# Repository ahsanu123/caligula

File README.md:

# 🥡 Introduction 

 <br/>
 
### 🎶 Useful Notes

```shell
To get started, you need to set up some environment variables by running: '. /home/ah/export-esp.sh'
This step must be done every time you open a new terminal.
See other methods for setting the environment in https://esp-rs.github.io/book/installation/riscv-and-xtensa.html#3-set-up-the-environment-variables
```

- to use usb from windows inside wsl you need bridge usb device from windows to wsl with `usbipd`

  ```shell
  C:\Windows\System32> usbipd list
  Connected:
  BUSID  VID:PID    DEVICE                                                        STATE
  1-1    feed:0ffa  USB Input Device                                              Not shared
  1-2    0000:3825  USB Input Device                                              Not shared
  1-4    0bda:0129  Realtek USB 2.0 Card Reader                                   Not shared
  1-5    13d3:56cb  USB2.0 HD IR UVC WebCam                                       Not shared
  1-6    1366:0101  J-Link driver                                                 Not shared
  1-10   8087:0026  Intel(R) Wireless Bluetooth(R)                                Not shared

  Persisted:
  GUID                                  DEVICE

  C:\Windows\System32> usbipd bind --busid 1-6

  C:\Windows\System32> usbipd attach --wsl --busid 1-6
  usbipd: info: Using WSL distribution 'Arch' to attach; the device will be available in all WSL 2 distributions.
  usbipd: info: Detected networking mode 'nat'.
  usbipd: info: Using IP address 172.27.144.1 to reach the host.

  C:\Windows\System32>
  ```

  then you can access the usb device as in linux

- run `get_esprs` to add needed compiler to system PATH (`alias get_esprs='export-esp.sh'`)
- to build release, flash, and monitor run `cargo run --release`, it will run runner `espflash  flash --monitor -L defmt` from Config.toml inside `.cargo` folder
- to run monitor only (no build) run `espflash monitor -L defmt --elf target/xtensa-esp32-none-elf/release/caligula`, you need add -L for logging format, and add --elf for defmt know about program.
- run `espflash board-info` to get connected board information
- to flash and run, `cargo run --release --bin rust_file_name.rs`
- embassy-sync blog -> https://blog.theembeddedrustacean.com/sharing-data-among-tasks-in-rust-embassy-synchronization-primitives

### 🧑‍🍳 Recipes

- esp-generate -> to scafold esp32 project [repo](https://github.com/esp-rs/esp-generate/)
- espup -> setup rust esp32 toolchain [repo](https://github.com/esp-rs/espup)
- defmt -> test like std rust in no_std [repo](https://github.com/knurling-rs/defmt)
- espflash -> to flashing firmware 
- probe-rs -> to debugging also able to flash

### 🪗 TODO Log

learn rust embassy ecosistem with esp-rs 

- ~~map all predefined SORE button and led~~
- ~~read multithread chapter in rust book~~
- ~~learn to make peripheral with hal~~
- learn about interupt and ~~dma~~
- ~~learn how embassy and esp-hal is connected~~
- ~~learn and explore embassy docs for esp32~~
- ~~read embassy_sync for multithread in embassy~~
- ~~learn embassy feature and learn embassy async~~
- search for match sensor and actuator
- make TMC2209 Stepper motor driver for actuator

### 🌴 Project Log

- 23 march 2025 20:02, basic esp rust setup with embassy, esp-println and defmt for logging is work
- ⛑️ TOOD: make project to have test like std rust with defmt, so its easier to create and unit testing in no_std
- 10 Mei 2025 13:06, done skiming https://docs.esp-rs.org/book
- 1 Mei 2026 18:10, finish routing phase one 

### 🌼 Reference 

- [esp no_std training](https://github.com/esp-rs/no_std-training)
- [official esp32 rust docs](https://docs.espressif.com/projects/rust/)
- [probe-rs](https://github.com/probe-rs/rusty-probe?tab=readme-ov-file)
- [rust-embedded](https://docs.rust-embedded.org/book/intro/tooling.html)
- [embassy-setup-on-esp32](https://pg3.dev/post/13)
- [plotter rs, console backend sample](https://github.com/plotters-rs/plotters/blob/master/plotters/examples/console.rs)
- [embassy-book](https://embassy.dev/book/)
- [esp-build](https://github.com/esp-rs/rust-build)
- https://github.com/zpg6/esp32-sdcard
- https://github.com/rust-embedded-community/embedded-sdmmc-rs
- [designing with ph electrodes](https://www.ti.com/lit/an/snoa529a/snoa529a.pdf)
- [tauri sidecar](https://tauri.app/develop/sidecar/)

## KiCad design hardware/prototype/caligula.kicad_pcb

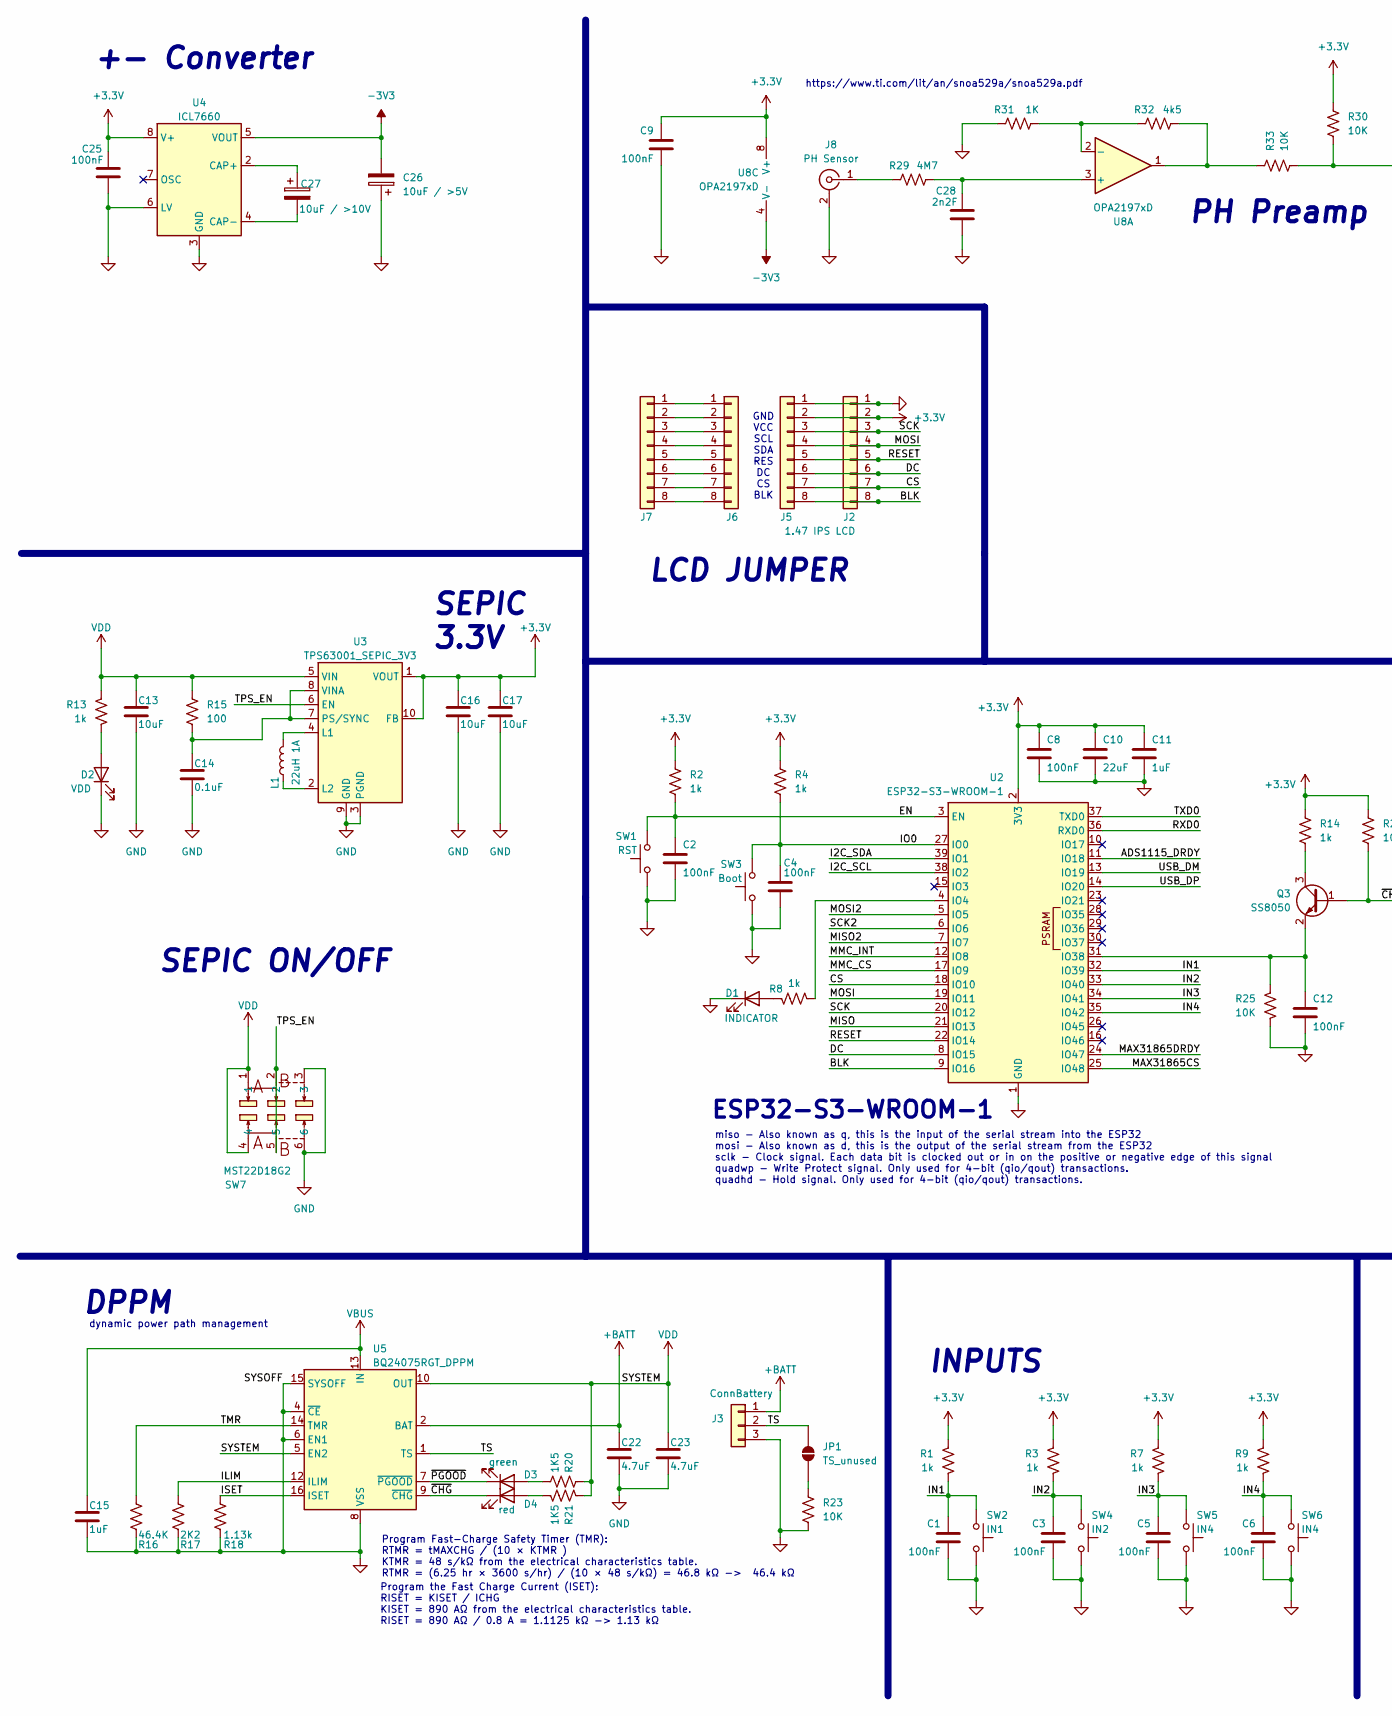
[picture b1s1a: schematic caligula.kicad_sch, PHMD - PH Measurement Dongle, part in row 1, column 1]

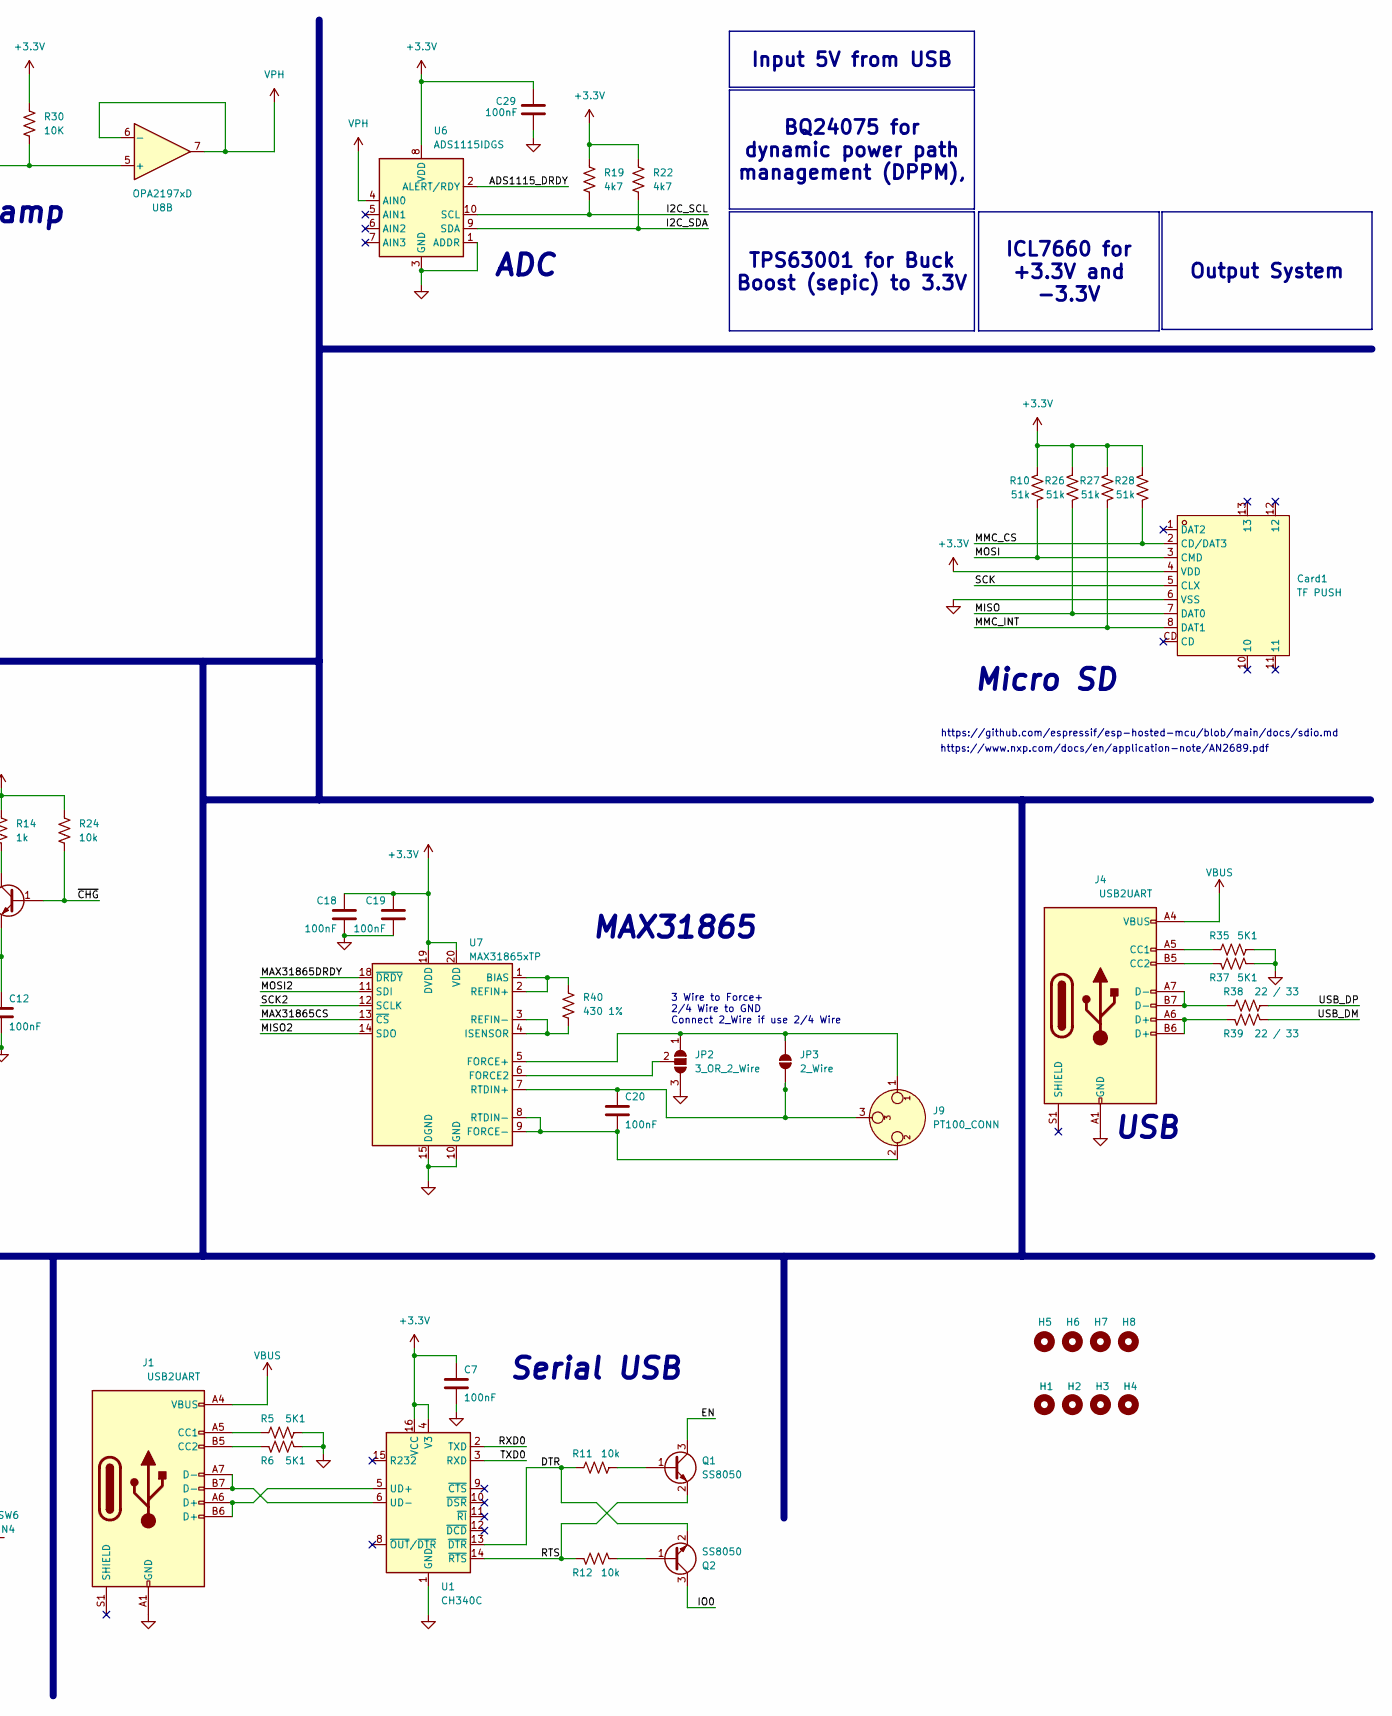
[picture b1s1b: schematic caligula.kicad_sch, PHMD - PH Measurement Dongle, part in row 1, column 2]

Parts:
C1, C2, C3, C4, C5, C6, C7, C8, C9, C12, C18, C19, C20, C25, C29: 100nF; C_0805_2012Metric_Pad1.18x1.45mm_HandSolder
C10: 22uF; C_0805_2012Metric_Pad1.18x1.45mm_HandSolder
C11, C15: 1uF; C_0805_2012Metric_Pad1.18x1.45mm_HandSolder
C13, C16, C17: 10uF; C_0805_2012Metric_Pad1.18x1.45mm_HandSolder
C14: 0.1uF; C_0805_2012Metric_Pad1.18x1.45mm_HandSolder
C22, C23: 4.7uF; C_0805_2012Metric_Pad1.18x1.45mm_HandSolder
C26: 10uF / >5V; C_0805_2012Metric_Pad1.18x1.45mm_HandSolder
C27: 10uF / >10V; C_0805_2012Metric_Pad1.18x1.45mm_HandSolder
C28: 2n2F; C_0805_2012Metric_Pad1.18x1.45mm_HandSolder
Card1: TF PUSH; TF-SMD_TF-PUSH; MPN TF PUSH; LCSC Part C393941
D1: INDICATOR; LED_1206_3216Metric_Pad1.42x1.75mm_HandSolder
D2: VDD; LED_1206_3216Metric_Pad1.42x1.75mm_HandSolder
D3: green; LED_0805_2012Metric_Pad1.15x1.40mm_HandSolder
D4: red; LED_0805_2012Metric_Pad1.15x1.40mm_HandSolder
H1, H2, H3, H4: MountingHole; MountingHole_2mm
H5, H6, H7, H8: MountingHole; MountingHole_3.2mm_M3
J1, J4: USB2UART; USB_C_Receptacle_GCT_USB4110
J2: 1.47 IPS LCD; PinHeader_1x08_P2.54mm_Vertical
J3: ConnBattery; JST_XH_S3B-XH-A_1x03_P2.50mm_Horizontal
J5, J6, J7: lcd jumper; PinHeader_1x08_P2.54mm_Vertical
J8: PH Sensor; BNC_Amphenol_B6252HB-NPP3G-50_Horizontal
J9: PT100_CONN; Jack_XLR_Neutrik_NC3FAH-0_Horizontal
JP1: TS_unused; SolderJumper-2_P1.3mm_Open_RoundedPad1.0x1.5mm
JP2: 3_OR_2_Wire; SolderJumper-3_P1.3mm_Open_RoundedPad1.0x1.5mm
JP3: 2_Wire; SolderJumper-2_P1.3mm_Open_TrianglePad1.0x1.5mm
L1: 22uH 1A; L_Bourns_SRP7028A_7.3x6.6mm
Q1, Q2, Q3: SS8050; SOT-23_Handsoldering
R1, R2, R3, R4, R7, R8, R9, R13, R14: 1k; R_0805_2012Metric_Pad1.20x1.40mm_HandSolder
R5, R6, R35, R37: 5K1; R_0805_2012Metric_Pad1.20x1.40mm_HandSolder
R10, R26, R27, R28: 51k; R_0805_2012Metric_Pad1.20x1.40mm_HandSolder
R11, R12, R24: 10k; R_0805_2012Metric_Pad1.20x1.40mm_HandSolder
R15: 100; R_0805_2012Metric_Pad1.20x1.40mm_HandSolder
R16: 46.4K; R_0805_2012Metric_Pad1.20x1.40mm_HandSolder
R17: 2K2; R_0805_2012Metric_Pad1.20x1.40mm_HandSolder
R18: 1.13k; R_0805_2012Metric_Pad1.20x1.40mm_HandSolder
R19, R22: 4k7; R_0805_2012Metric_Pad1.20x1.40mm_HandSolder
R20, R21: 1K5; R_0805_2012Metric_Pad1.20x1.40mm_HandSolder
R23, R25, R30, R33: 10K; R_0805_2012Metric_Pad1.20x1.40mm_HandSolder
R29: 4M7; R_0805_2012Metric_Pad1.20x1.40mm_HandSolder
R31: 1K; R_0805_2012Metric_Pad1.20x1.40mm_HandSolder
R32: 4k5; R_0805_2012Metric_Pad1.20x1.40mm_HandSolder
R38, R39: 22 / 33; R_0805_2012Metric_Pad1.20x1.40mm_HandSolder
R40: 430 1%; R_0805_2012Metric_Pad1.20x1.40mm_HandSolder
SW1: RST; SW_SPST_EVQP7A
SW2: IN1; Kailh_socket_MX_reversible_platemount
SW3: Boot; SW_SPST_EVQP7A
SW4: IN2; Kailh_socket_MX_reversible_platemount
SW5, SW6: IN4; Kailh_socket_MX_reversible_platemount
SW7: MST22D18G2; SW-SMD_MST22D18G2; MPN MST22D18G2; LCSC Part C431544
U1: CH340C; SOIC-16_3.9x9.9mm_P1.27mm
U2: ESP32-S3-WROOM-1
U3: TPS63001_SEPIC_3V3; Texas_DRC0010J_ThermalVias
U4: ICL7660; SOIC-8_3.9x4.9mm_P1.27mm
U5: BQ24075RGT_DPPM; VQFN-16-1EP_3x3mm_P0.5mm_EP1.6x1.6mm
U6: ADS1115IDGS; TSSOP-10_3x3mm_P0.5mm
U7: MAX31865xTP; TQFN-20-1EP_5x5mm_P0.65mm_EP3.25x3.25mm
U8: OPA2197xD; SOIC-8_3.9x4.9mm_P1.27mm

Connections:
+3.3V: C7.1, C8.1, C9.1, C10.1, C11.1, C16.1, C17.1, C18.1, C19.1, C25.1, C29.1, Card1.4 (VDD), J2.2, J5.2, R1.1, R2.1, R3.1, R4.1, R7.1, R9.1, R10.1, R14.1, R19.1, R22.1, R24.1, R26.1, R27.1, R28.1, R30.1, U1.4 (V3), U1.16 (VCC), U2.2 (3V3), U3.1 (VOUT), U3.10 (FB), U4.8 (V+), U6.8 (VDD), U7.19 (DVDD), U7.20 (VDD), U8.8 (V+)
+BATT: C22.1, J3.1, U5.2 (BAT), U5.3 (BAT)
-3V3: C26.2, U4.5 (VOUT), U8.4 (V-)
/ADS1115_DRDY: U2.11 (IO18), U6.2 (ALERT/RDY)
/BLK: J2.8, J5.8, U2.9 (IO16)
/CS: J2.7, J5.7, U2.18 (IO10)
/DC: J2.6, J5.6, U2.8 (IO15)
/DTR: Q2.2 (E), R11.2, U1.13 (~DTR)
/EN: C2.1, Q1.3 (C), R2.2, SW1.2, U2.3 (EN)
/I2C_SCL: R19.2, U2.38 (IO2), U6.10 (SCL)
/I2C_SDA: R22.2, U2.39 (IO1), U6.9 (SDA)
/ILIM: R17.1, U5.12 (ILIM)
/IN1: C1.1, R1.2, SW2.2, U2.32 (IO39)
/IN2: C3.1, R3.2, SW4.2, U2.33 (IO40)
/IN3: C5.1, R7.2, SW5.2, U2.34 (IO41)
/IN4: C6.1, R9.2, SW6.2, U2.35 (IO42)
/IO0: C4.1, Q2.3 (C), R4.2, SW3.2, U2.27 (IO0)
/ISET: R18.1, U5.16 (ISET)
/MAX31865CS: U2.25 (IO48), U7.13 (~CS)
/MAX31865DRDY: U2.24 (IO47), U7.18 (~DRDY)
/MISO: Card1.7 (DAT0), R26.2, U2.21 (IO13)
/MISO2: U2.7 (IO7), U7.14 (SDO)
/MMC_CS: Card1.2 (CD/DAT3), R28.2, U2.17 (IO9)
/MMC_INT: Card1.8 (DAT1), R27.2, U2.12 (IO8)
/MOSI: Card1.3 (CMD), J2.4, J5.4, R10.2, U2.19 (IO11)
/MOSI2: U2.5 (IO5), U7.11 (SDI)
/RESET: J2.5, J5.5, U2.22 (IO14)
/RTS: Q1.2 (E), R12.2, U1.14 (~RTS)
/RXD0: U1.2 (TXD), U2.36 (RXD0)
/SCK: Card1.5 (CLX), J2.3, J5.3, U2.20 (IO12)
/SCK2: U2.6 (IO6), U7.12 (SCLK)
/TMR: R16.1, U5.14 (TMR)
/TPS_EN: SW7.2, SW7.5, U3.6 (EN)
/TS: J3.2, JP1.2 (B), U5.1 (TS)
/TXD0: U1.3 (RXD), U2.37 (TXD0)
/USB_DM: R39.1, U2.13 (IO19)
/USB_DP: R38.1, U2.14 (IO20)
/~CHG: D4.1 (K), Q3.1 (B), R24.2, U5.9 (~CHG)
/~PGOOD: D3.1 (K), U5.7 (~PGOOD)
GND: C1.2, C2.2, C3.2, C4.2, C5.2, C6.2, C7.2, C8.2, C9.2, C10.2, C11.2, C12.2, C13.2, C14.2, C15.2, C16.2, C17.2, C18.2, C19.2, C22.2, C23.2, C25.2, C26.1, C28.2, C29.2, Card1.6 (VSS), D1.1 (K), D2.1 (K), J1.A1 (GND), J1.A12 (GND), J1.B1 (GND), J1.B12 (GND), J2.1, J3.3, J4.A1 (GND), J4.A12 (GND), J4.B1 (GND), J4.B12 (GND), J5.1, J8.2 (Ext), JP2.3 (B), R5.1, R6.1, R16.2, R17.2, R18.2, R23.2, R25.2, R31.2, R35.1, R37.1, SW1.1, SW2.1, SW3.1, SW4.1, SW5.1, SW6.1, SW7.3, SW7.6, U1.1 (GND), U2.1 (GND), U2.40 (GND), U2.41 (GND), U3.3 (PGND), U3.9 (GND), U3.11 (PGND), U4.3 (GND), U4.6 (LV), U5.4 (~CE), U5.6 (EN1), U5.8 (VSS), U5.15 (SYSOFF), U5.17 (VSS), U6.1 (ADDR), U6.3 (GND), U7.10 (GND), U7.15 (DGND), U7.16 (GND), U7.21 (GND)
unnamed: D1.2 (A), R8.1
unnamed: D2.2 (A), R13.2
unnamed: D3.2 (A), R20.1
unnamed: D4.2 (A), R21.1
unnamed: J1.A5 (CC1), R5.2
unnamed: J1.B5 (CC2), R6.2
unnamed: J4.A5 (CC1), R35.2
unnamed: J4.B5 (CC2), R37.2
unnamed: J4.A6 (D+), J4.B6 (D+), R39.2
unnamed: J4.A7 (D-), J4.B7 (D-), R38.2
unnamed: J6.1, J7.1
unnamed: J6.2, J7.2
unnamed: J6.3, J7.3
unnamed: J6.4, J7.4
unnamed: J6.5, J7.5
unnamed: J6.6, J7.6
unnamed: J6.7, J7.7
unnamed: J6.8, J7.8
unnamed: J8.1 (In), R29.2
unnamed: JP1.1 (A), R23.1
unnamed: J9.1, JP2.1 (A), JP3.2 (B), U7.5 (FORCE+)
unnamed: JP2.2 (C), U7.6 (FORCE2)
unnamed: C20.1, J9.3, JP3.1 (A), U7.7 (RTDIN+)
unnamed: Q1.1 (B), R11.1
unnamed: Q2.1 (B), R12.1
unnamed: Q3.3 (C), R14.2
unnamed: C12.1, Q3.2 (E), R25.1, U2.31 (IO38)
unnamed: R32.1, R33.1, U8.1
unnamed: J1.A6 (D+), J1.B6 (D+), U1.5 (UD+)
unnamed: J1.A7 (D-), J1.B7 (D-), U1.6 (UD-)
unnamed: R8.2, U2.4 (IO4)
unnamed: L1.2, U3.4 (L1)
unnamed: L1.1, U3.2 (L2)
unnamed: C14.1, R15.2, U3.7 (PS/SYNC), U3.8 (VINA)
unnamed: C27.1, U4.2 (CAP+)
unnamed: C27.2, U4.4 (CAP-)
unnamed: R40.1, U7.1 (BIAS), U7.2 (REFIN+)
unnamed: C20.2, J9.2, U7.8 (RTDIN-), U7.9 (FORCE-)
unnamed: R40.2, U7.3 (REFIN-), U7.4 (ISENSOR)
unnamed: C28.1, R29.1, U8.3 (+)
unnamed: R31.1, R32.2, U8.2 (-)
unnamed: R30.2, R33.2, U8.5 (+)
VBUS: C15.1, J1.A4 (VBUS), J1.A9 (VBUS), J1.B4 (VBUS), J1.B9 (VBUS), J4.A4 (VBUS), J4.A9 (VBUS), J4.B4 (VBUS), J4.B9 (VBUS), U5.13 (IN)
VDD: C13.1, C23.1, R13.1, R15.1, R20.2, R21.2, SW7.1, SW7.4, U3.5 (VIN), U5.5 (EN2), U5.10 (OUT), U5.11 (OUT)
VPH: U6.4 (AIN0), U8.6 (-), U8.7

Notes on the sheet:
ADC
dynamic power path management
SEPIC ON/OFF
https://www.nxp.com/docs/en/application-note/AN2689.pdf
PH Preamp
miso - Also known as q, this is the input of the serial stream into the ESP32 mosi - Also known as d, this is the output of the serial stream from the ESP32 sclk - Clock signal. Each data bit is clocked out or in on the positive or negative edge of this signal quadwp - Write Protect signal. Only us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
ESP32-S3-WROOM-1
Serial USB
Program the Fast Charge Current (ISET): RISET = KISET / ICHG KISET = 890 AΩ from the electrical characteristics table. RISET = 890 AΩ / 0.8 A = 1.1125 kΩ -> 1.13 kΩ
3 Wire to Force+ 2/4 Wire to GND Connect 2_Wire if use 2/4 Wire
USB
+- Converter
https://www.ti.com/lit/an/snoa529a/snoa529a.pdf
DPPM
GND VCC SCL SDA RES DC CS BLK
https://github.com/espressif/esp-hosted-mcu/blob/main/docs/sdio.md
MAX31865
INPUTS
LCD JUMPER
SEPIC 3.3V
Micro SD
Program Fast-Charge Safety Timer (TMR): RTMR = tMAXCHG / (10 × KTMR ) KTMR = 48 s/kΩ from the electrical characteristics table. RTMR = (6.25 hr × 3600 s/hr) / (10 × 48 s/kΩ) = 46.8 kΩ -> 46.4 kΩ
Output System
TPS63001 for Buck Boost (sepic) to 3.3V
ICL7660 for +3.3V and -3.3V
Input 5V from USB
BQ24075 for dynamic power path management (DPPM),

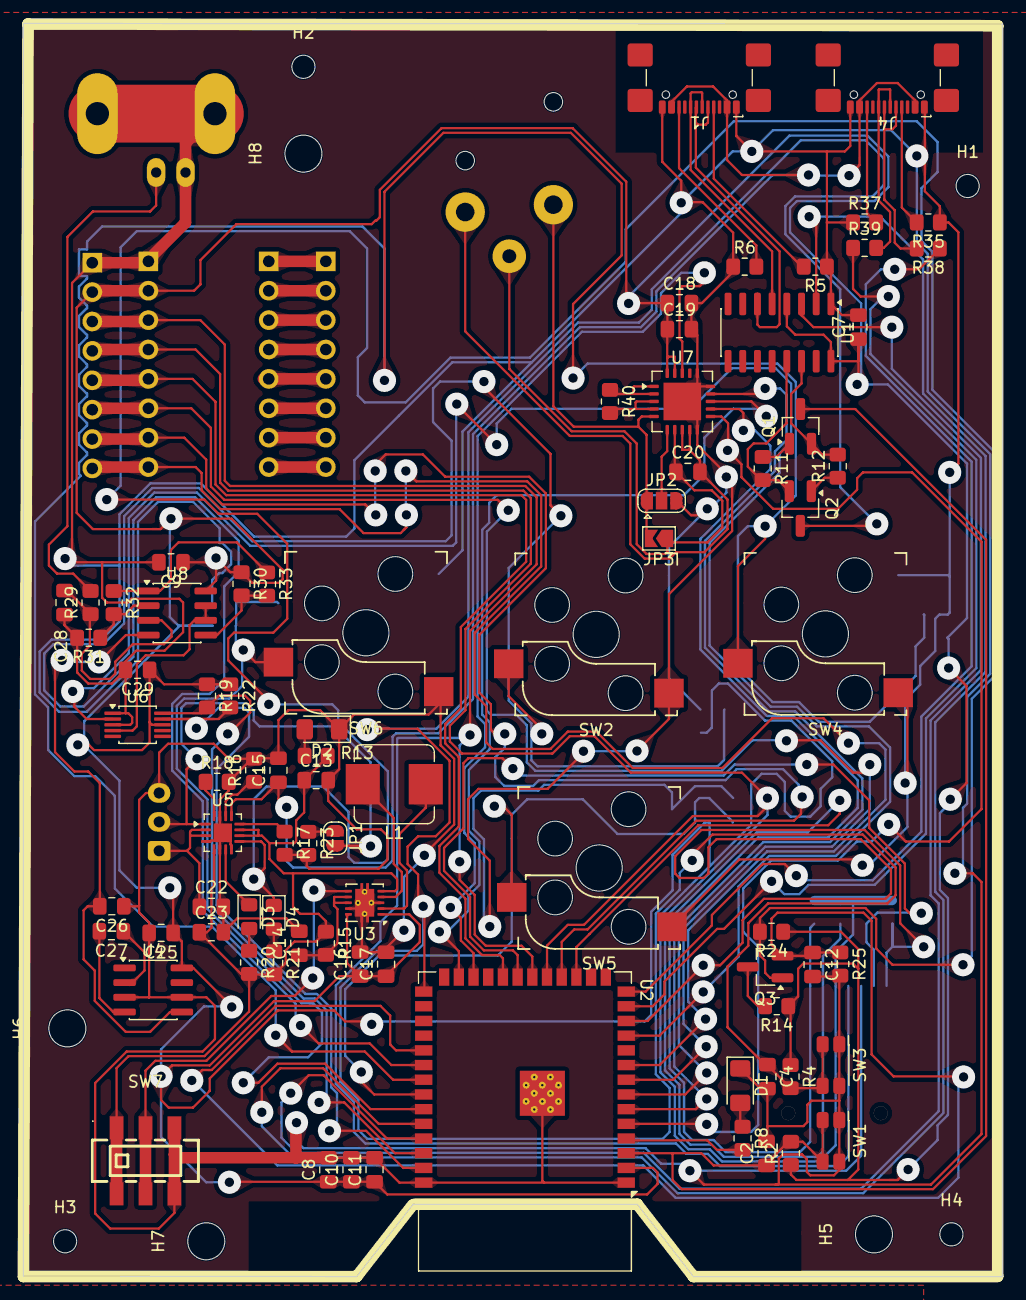
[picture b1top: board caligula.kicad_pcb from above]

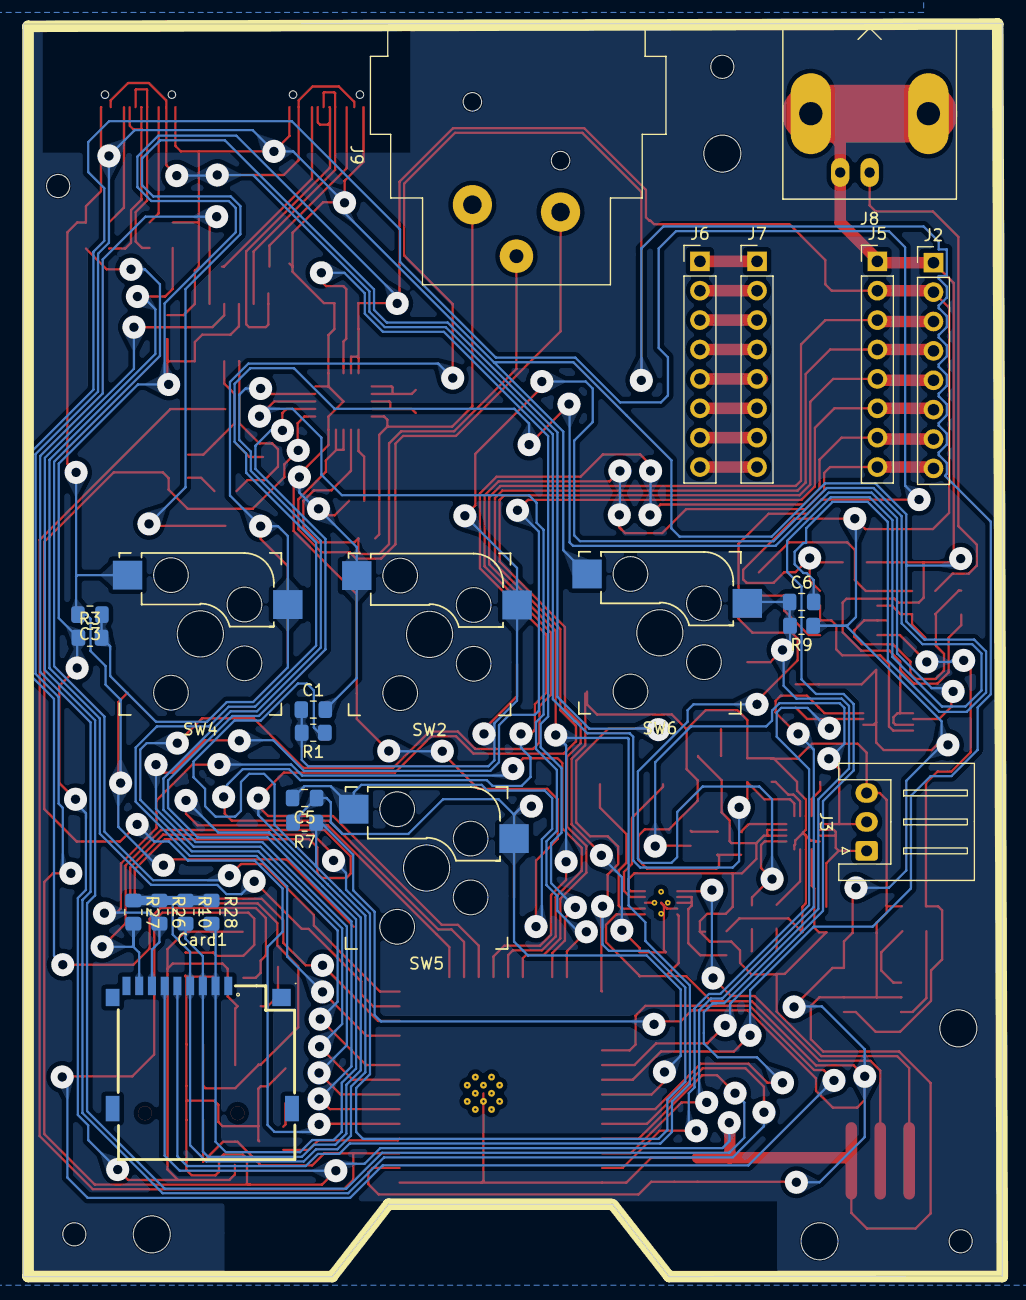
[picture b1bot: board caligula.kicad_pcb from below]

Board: 2 copper layers, 84.6 x 108.3 mm, 109 parts (24 on the bottom side), 85 nets.

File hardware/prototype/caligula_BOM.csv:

"Reference","Qty","Value","DNP","Exclude from BOM","Exclude from Board","Footprint","Datasheet"
"C1,C2,C3,C4,C5,C6,C7,C8,C9,C12,C18,C19,C20,C25,C29","15","100nF","","","","Capacitor_SMD:C_0805_2012Metric_Pad1.18x1.45mm_HandSolder",""
"C10","1","22uF","","","","Capacitor_SMD:C_0805_2012Metric_Pad1.18x1.45mm_HandSolder",""
"C11,C15","2","1uF","","","","Capacitor_SMD:C_0805_2012Metric_Pad1.18x1.45mm_HandSolder",""
"C13,C16,C17","3","10uF","","","","Capacitor_SMD:C_0805_2012Metric_Pad1.18x1.45mm_HandSolder",""
"C14","1","0.1uF","","","","Capacitor_SMD:C_0805_2012Metric_Pad1.18x1.45mm_HandSolder",""
"C22,C23","2","4.7uF","","","","Capacitor_SMD:C_0805_2012Metric_Pad1.18x1.45mm_HandSolder",""
"C26","1","10uF / >5V","","","","Capacitor_SMD:C_0805_2012Metric_Pad1.18x1.45mm_HandSolder",""
"C27","1","10uF / >10V","","","","Capacitor_SMD:C_0805_2012Metric_Pad1.18x1.45mm_HandSolder",""
"C28","1","2n2F","","","","Capacitor_SMD:C_0805_2012Metric_Pad1.18x1.45mm_HandSolder",""
"Card1","1","TF PUSH","","","","easyeda2kicad:TF-SMD_TF-PUSH","https://lcsc.com/product-detail/Connector-Card-Sockets_SHOU-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"
"D1","1","INDICATOR","","","","LED_SMD:LED_1206_3216Metric_Pad1.42x1.75mm_HandSolder",""
"D2","1","VDD","","","","LED_SMD:LED_1206_3216Metric_Pad1.42x1.75mm_HandSolder",""
"D3","1","green","","","","LED_SMD:LED_0805_2012Metric_Pad1.15x1.40mm_HandSolder",""
"D4","1","red","","","","LED_SMD:LED_0805_2012Metric_Pad1.15x1.40mm_HandSolder",""
"J1,J4","2","USB2UART","","","","Connector_USB:USB_C_Receptacle_GCT_USB4110","https://www.usb.org/sites/default/files/documents/usb_type-c.zip"
"J2","1","1.47 IPS LCD","","","","Connector_PinHeader_2.54mm:PinHeader_1x08_P2.54mm_Vertical",""
"J3","1","ConnBattery","","","","Connector_JST:JST_XH_S3B-XH-A_1x03_P2.50mm_Horizontal",""
"J5,J6,J7","3","lcd jumper","","","","Connector_PinHeader_2.54mm:PinHeader_1x08_P2.54mm_Vertical",""
"J8","1","PH Sensor","","","","Connector_Coaxial:BNC_Amphenol_B6252HB-NPP3G-50_Horizontal",""
"J9","1","PT100_CONN","","","","Connector_Audio:Jack_XLR_Neutrik_NC3FAH-0_Horizontal",""
"L1","1","22uH 1A","","","","Inductor_SMD:L_Bourns_SRP7028A_7.3x6.6mm",""
"Q1,Q2,Q3","3","SS8050","","","","Package_TO_SOT_SMD:SOT-23_Handsoldering","https://www.onsemi.com/pub/Collateral/BC818-D.pdf"
"R1,R2,R3,R4,R7,R8,R9,R13,R14","9","1k","","","","Resistor_SMD:R_0805_2012Metric_Pad1.20x1.40mm_HandSolder",""
"R5,R6,R35,R37","4","5K1","","","","Resistor_SMD:R_0805_2012Metric_Pad1.20x1.40mm_HandSolder",""
"R10,R26,R27,R28","4","51k","","","","Resistor_SMD:R_0805_2012Metric_Pad1.20x1.40mm_HandSolder",""
"R11,R12,R24","3","10k","","","","Resistor_SMD:R_0805_2012Metric_Pad1.20x1.40mm_HandSolder",""
"R15","1","100","","","","Resistor_SMD:R_0805_2012Metric_Pad1.20x1.40mm_HandSolder",""
"R16","1","46.4K","","","","Resistor_SMD:R_0805_2012Metric_Pad1.20x1.40mm_HandSolder",""
"R17","1","2K2","","","","Resistor_SMD:R_0805_2012Metric_Pad1.20x1.40mm_HandSolder",""
"R18","1","1.13k","","","","Resistor_SMD:R_0805_2012Metric_Pad1.20x1.40mm_HandSolder",""
"R19,R22","2","4k7","","","","Resistor_SMD:R_0805_2012Metric_Pad1.20x1.40mm_HandSolder",""
"R20,R21","2","1K5","","","","Resistor_SMD:R_0805_2012Metric_Pad1.20x1.40mm_HandSolder",""
"R23,R25,R30,R33","4","10K","","","","Resistor_SMD:R_0805_2012Metric_Pad1.20x1.40mm_HandSolder",""
"R29","1","4M7","","","","Resistor_SMD:R_0805_2012Metric_Pad1.20x1.40mm_HandSolder",""
"R31","1","1K","","","","Resistor_SMD:R_0805_2012Metric_Pad1.20x1.40mm_HandSolder",""
"R32","1","4k5","","","","Resistor_SMD:R_0805_2012Metric_Pad1.20x1.40mm_HandSolder",""
"R38,R39","2","22 / 33","","","","Resistor_SMD:R_0805_2012Metric_Pad1.20x1.40mm_HandSolder",""
"R40","1","430 1%","","","","Resistor_SMD:R_0805_2012Metric_Pad1.20x1.40mm_HandSolder",""
"SW1","1","RST","","","","Button_Switch_SMD:SW_SPST_EVQP7A",""
"SW2","1","IN1","","","","keyswitches.pretty-master:Kailh_socket_MX_reversible_platemount",""
"SW3","1","Boot","","","","Button_Switch_SMD:SW_SPST_EVQP7A",""
"SW4","1","IN2","","","","keyswitches.pretty-master:Kailh_socket_MX_reversible_platemount",""
"SW5,SW6","2","IN4","","","","keyswitches.pretty-master:Kailh_socket_MX_reversible_platemount",""
"SW7","1","MST22D18G2","","","","easyeda2kicad:SW-SMD_MST22D18G2","https://www.lcsc.com/datasheet/C431544.pdf"
"U1","1","CH340C","","","","Package_SO:SOIC-16_3.9x9.9mm_P1.27mm","https://datasheet.lcsc.com/szlcsc/Jiangsu-Qin-Heng-CH340C_C8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"
"U2","1","ESP32-S3-WROOM-1","","","","RF_Module:ESP32-S3-WROOM-1","https://www.espressif.com/sites/default/files/documentation/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"
"U3","1","TPS63001_SEPIC_3V3","","","","Package_SON:Texas_DRC0010J_ThermalVias","http://www.ti.com/lit/ds/symlink/tps63000.pdf"
"U4","1","ICL7660","","","","Package_SO:SOIC-8_3.9x4.9mm_P1.27mm","http://datasheets.maximintegrated.com/en/ds/ICL7660-MAX1044.pdf"
"U5","1","BQ24075RGT_DPPM","","","","Package_DFN_QFN:VQFN-16-1EP_3x3mm_P0.5mm_EP1.6x1.6mm","http://www.ti.com/lit/ds/symlink/bq24075.pdf"
"U6","1","ADS1115IDGS","","","","Package_SO:TSSOP-10_3x3mm_P0.5mm","http://www.ti.com/lit/ds/symlink/ads1113.pdf"
"U7","1","MAX31865xTP","","","","Package_DFN_QFN:TQFN-20-1EP_5x5mm_P0.65mm_EP3.25x3.25mm","https://datasheets.maximintegrated.com/en/ds/MAX31865.pdf"
"U8","1","OPA2197xD","","","","Package_SO:SOIC-8_3.9x4.9mm_P1.27mm","http://www.ti.com/lit/ds/symlink/opa2197.pdf"

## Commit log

2025-03-23 [03-23-1403] initial commit of caligula
2025-03-24 [03-23-1958] basic logging with defmt and esp-println worked.
    Update README.md
    Update README.md
    Create caligula-logo.svg
    Update caligula-logo.svg
    Update caligula-logo.svg
    Update README.md
2025-05-10 [03-23-1958] basic logging with defmt and esp-println worked.
    Update README.md
    Update README.md
    Create caligula-logo.svg
    Update caligula-logo.svg
    Update caligula-logo.svg
    Update README.md
2025-05-10 [05-10-1327] start embassy learning
2025-05-10 [05-10-1518] add blinky with button
    add expanded
2025-06-11 [06-11-2043] add blank tmc2209 breakout kicad project
2025-06-12 [06-12-1437] create list poc of embassy sync
2025-06-12 [06-12-1605] add note of several embassy sync
2025-06-15 [06-15-2036] add mermaid diagram for several embassy sync
2025-06-15 [06-15-2233] make signal poc, not tested yet,
2025-06-16 [06-16-0705] basic signal poc worked
2025-07-03 [07-03-2154] able to run trouble in esp32
2025-11-10 chore: reorganized folder
2025-11-10 feat: add firmware cli
2025-11-10 chore: attempt to add embedded cli in esp32
2026-04-27 feat: start to doing simulation
2026-04-28 feat: ph sensor preamp simulation seem work correctly
2026-04-28 feat: start to work on electronics prototype
2026-04-28 feat: update simulation to use +- 3.6v
2026-04-28 chore: tidying up schematic
2026-04-29 feat: update component placement
2026-04-29 feat: start routing prototype
2026-04-30 feat: update routing phase 1
2026-04-30 feat: finish routing caligula proto v1
2026-05-01 feat: rechecking routing
2026-05-26 feat: reduce board size
2026-05-30 feat: initializing software
2026-05-30 feat: add caligula rust sidecar
2026-05-30 feat: add app slint project and surealism ui library
2026-05-31 feat: making simple architecture
2026-06-01 feat: simple shaku poc as configuration provider
2026-06-01 feat: able to hook shaku dependency injection to controller function
2026-06-01 feat: add connection_provider
